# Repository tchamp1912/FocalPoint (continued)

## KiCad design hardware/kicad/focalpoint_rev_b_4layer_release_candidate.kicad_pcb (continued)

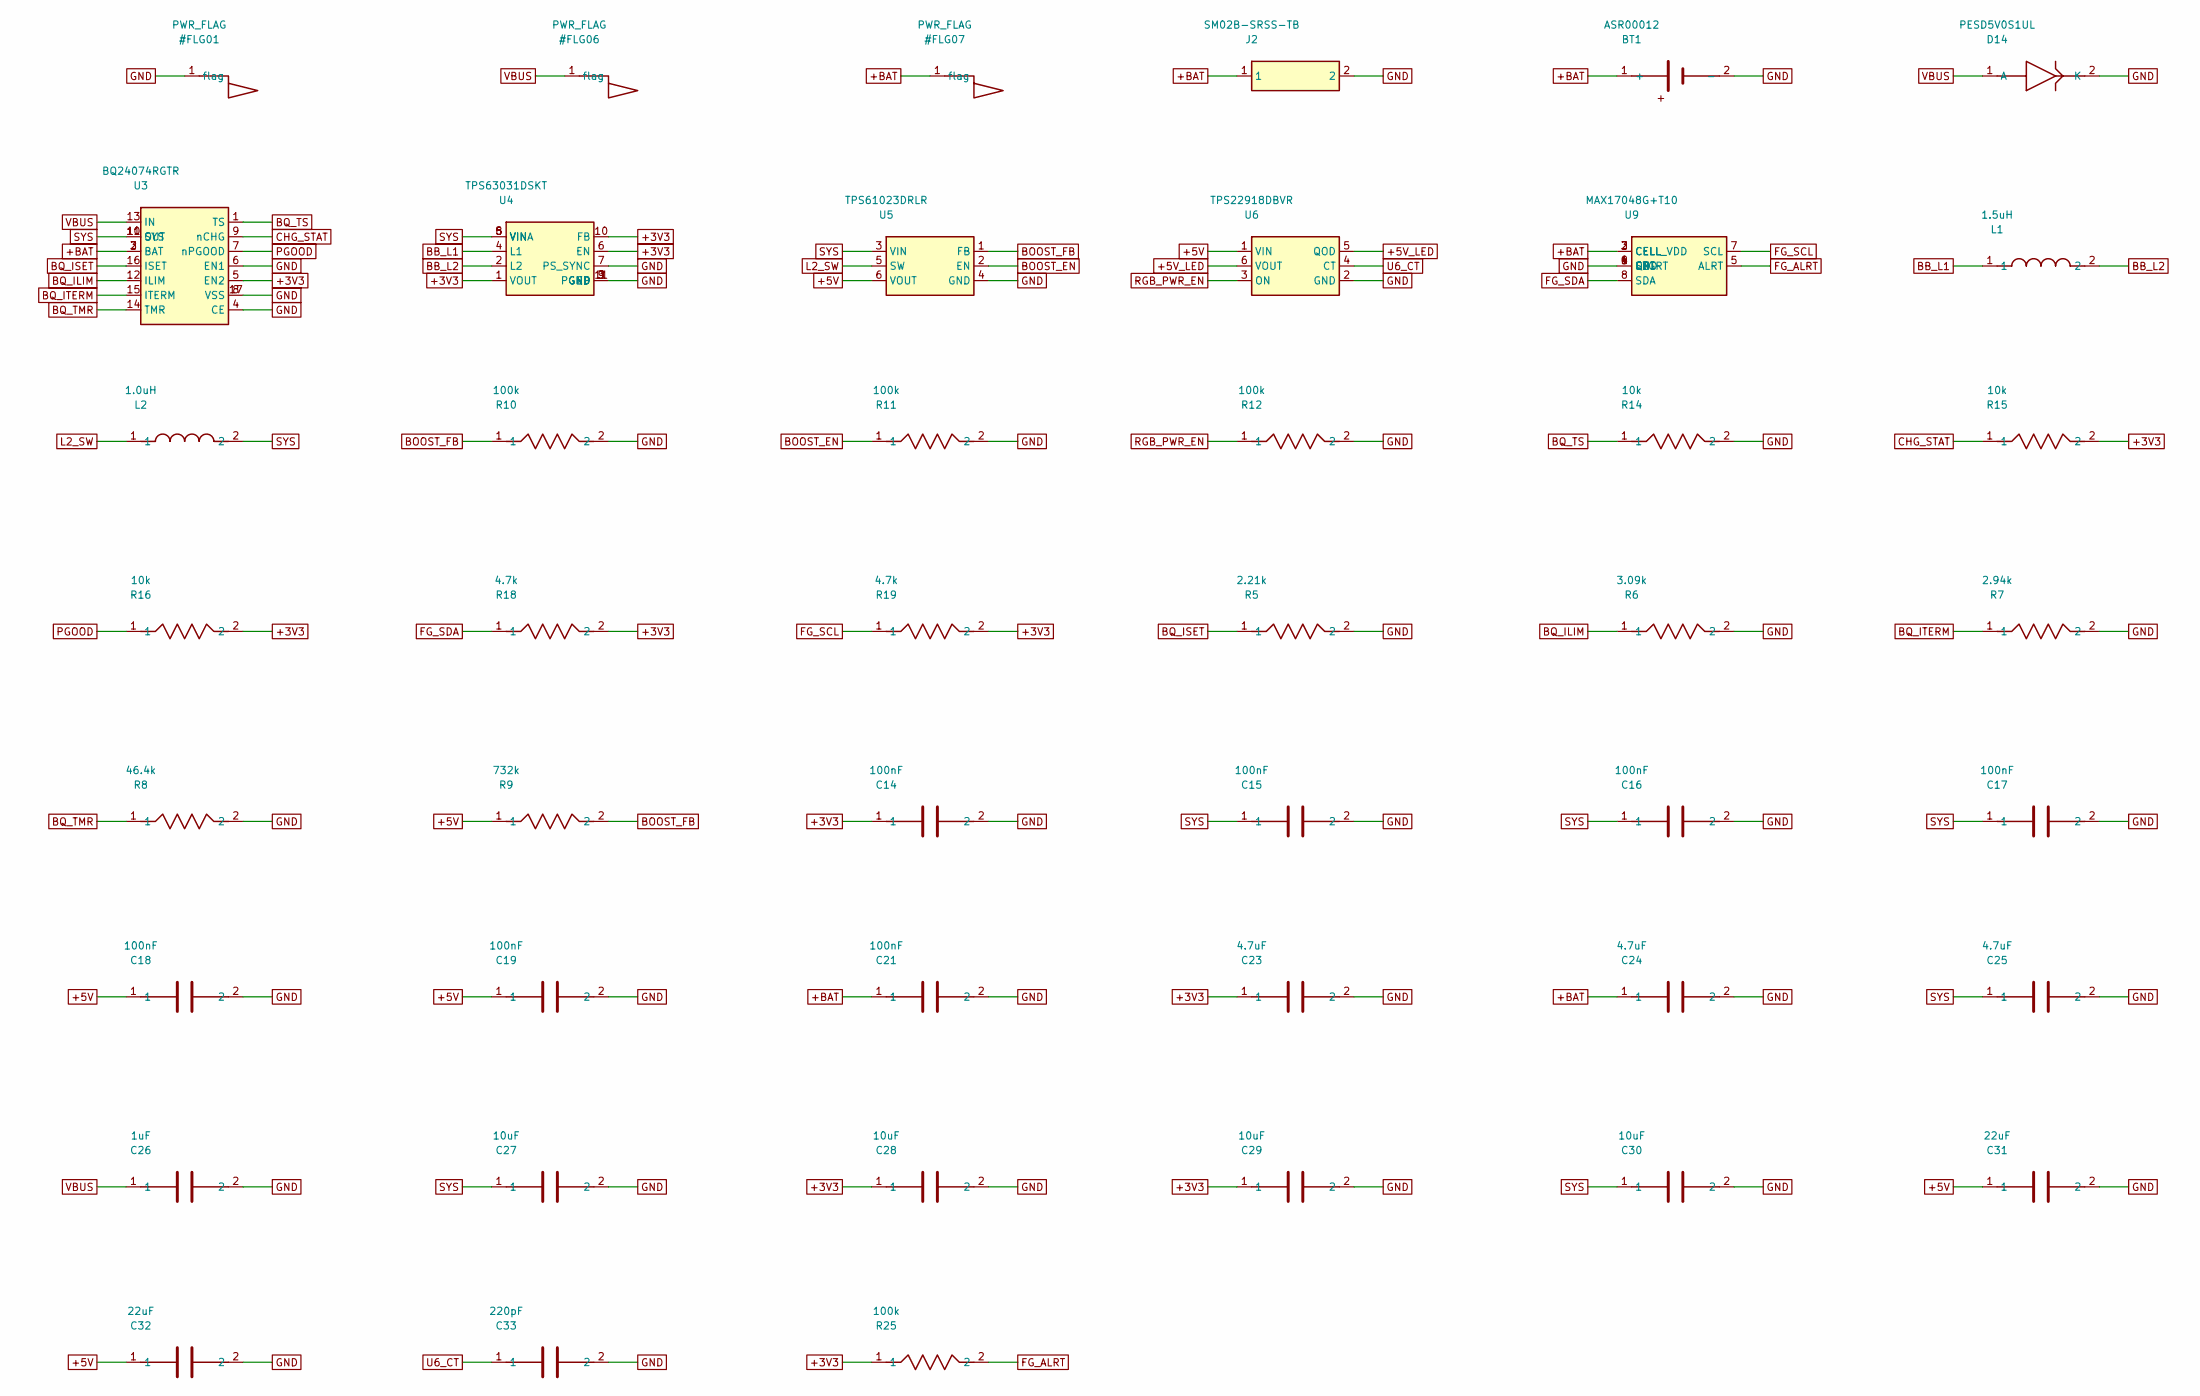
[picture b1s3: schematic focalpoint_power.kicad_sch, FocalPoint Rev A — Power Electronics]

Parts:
BT1: ASR00012
C14, C15, C16, C17, C18, C19, C21: 100nF; C_0603_1608Metric
C23, C24, C25: 4.7uF; C_0603_1608Metric
C26: 1uF; C_0603_1608Metric
C27, C28, C29, C30: 10uF; C_0603_1608Metric
C31, C32: 22uF; C_0603_1608Metric
C33: 220pF; C_0603_1608Metric
D14: PESD5V0S1UL; D_SOD-882
J2: SM02B-SRSS-TB; JST_SH_SM02B-SRSS-TB_1x02-1MP_P1.00mm_Horizontal
L1: 1.5uH; L_Sunlord_SWPA3015S
L2: 1.0uH; L_Sunlord_MWSA0402S
R5: 2.21k; R_0603_1608Metric
R6: 3.09k; R_0603_1608Metric
R7: 2.94k; R_0603_1608Metric
R8: 46.4k; R_0603_1608Metric
R9: 732k; R_0603_1608Metric
R10, R11, R12, R25: 100k; R_0603_1608Metric
R14, R15, R16: 10k; R_0603_1608Metric
R18, R19: 4.7k; R_0603_1608Metric
U3: BQ24074RGTR; VQFN-16-1EP_3x3mm_P0.5mm_EP1.68x1.68mm_ThermalVias
U4: TPS63031DSKT; WSON-10-1EP_2.5x2.5mm_P0.5mm_EP1.2x2mm_ThermalVias
U5: TPS61023DRLR; SOT-563
U6: TPS22918DBVR; SOT-23-6
U9: MAX17048G+T10; TDFN-8-1EP_2x2mm_P0.5mm_EP0.8x1.2mm

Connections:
+3V3: C14.1, C23.1, C28.1, C29.1, R15.2, R16.2, R18.2, R19.2, R25.1, U3.5 (EN2), U4.1 (VOUT), U4.6 (EN), U4.10 (FB); also elsewhere on the board
+5V: C18.1, C19.1, C31.1, C32.1, R9.1, U5.6 (VOUT), U6.1 (VIN); also elsewhere on the board
+5V_LED: U6.5 (QOD), U6.6 (VOUT); also elsewhere on the board
+BAT: BT1.1 (+), C21.1, C24.1, J2.1, U3.2 (BAT), U3.3 (BAT), U9.2 (CELL), U9.3 (CELL_VDD)
BB_L1: L1.1, U4.4 (L1)
BB_L2: L1.2, U4.2 (L2)
BOOST_EN: R11.1, U5.2 (EN); also elsewhere on the board
BOOST_FB: R9.2, R10.1, U5.1 (FB)
BQ_ILIM: R6.1, U3.12 (ILIM)
BQ_ISET: R5.1, U3.16 (ISET)
BQ_ITERM: R7.1, U3.15 (ITERM)
BQ_TMR: R8.1, U3.14 (TMR)
BQ_TS: R14.1, U3.1 (TS)
CHG_STAT: R15.1, U3.9 (nCHG); also elsewhere on the board
FG_ALRT: R25.2, U9.5 (ALRT); also elsewhere on the board
FG_SCL: R19.1, U9.7 (SCL); also elsewhere on the board
FG_SDA: R18.1, U9.8 (SDA); also elsewhere on the board
GND: BT1.2 (-), C14.2, C15.2, C16.2, C17.2, C18.2, C19.2, C21.2, C23.2, C24.2, C25.2, C26.2, C27.2, C28.2, C29.2, C30.2, C31.2, C32.2, C33.2, D14.2 (K), J2.2, R5.2, R6.2, R7.2, R8.2, R10.2, R11.2, R12.2, R14.2, U3.4 (CE), U3.6 (EN1), U3.8 (VSS), U3.17 (VSS), U4.3 (PGND), U4.7 (PS_SYNC), U4.9 (GND), U4.11 (EP), U5.4 (GND), U6.2 (GND), U9.1 (CTG), U9.4 (GND), U9.6 (QSTRT), U9.9 (EP); also elsewhere on the board
L2_SW: L2.1, U5.5 (SW)
PGOOD: R16.1, U3.7 (nPGOOD); also elsewhere on the board
RGB_PWR_EN: R12.1, U6.3 (ON); also elsewhere on the board
SYS: C15.1, C16.1, C17.1, C25.1, C27.1, C30.1, L2.2, U3.10 (SYS), U3.11 (OUT), U4.5 (VIN), U4.8 (VINA), U5.3 (VIN)
U6_CT: C33.1, U6.4 (CT)
VBUS: C26.1, D14.1 (A), U3.13 (IN); also elsewhere on the board

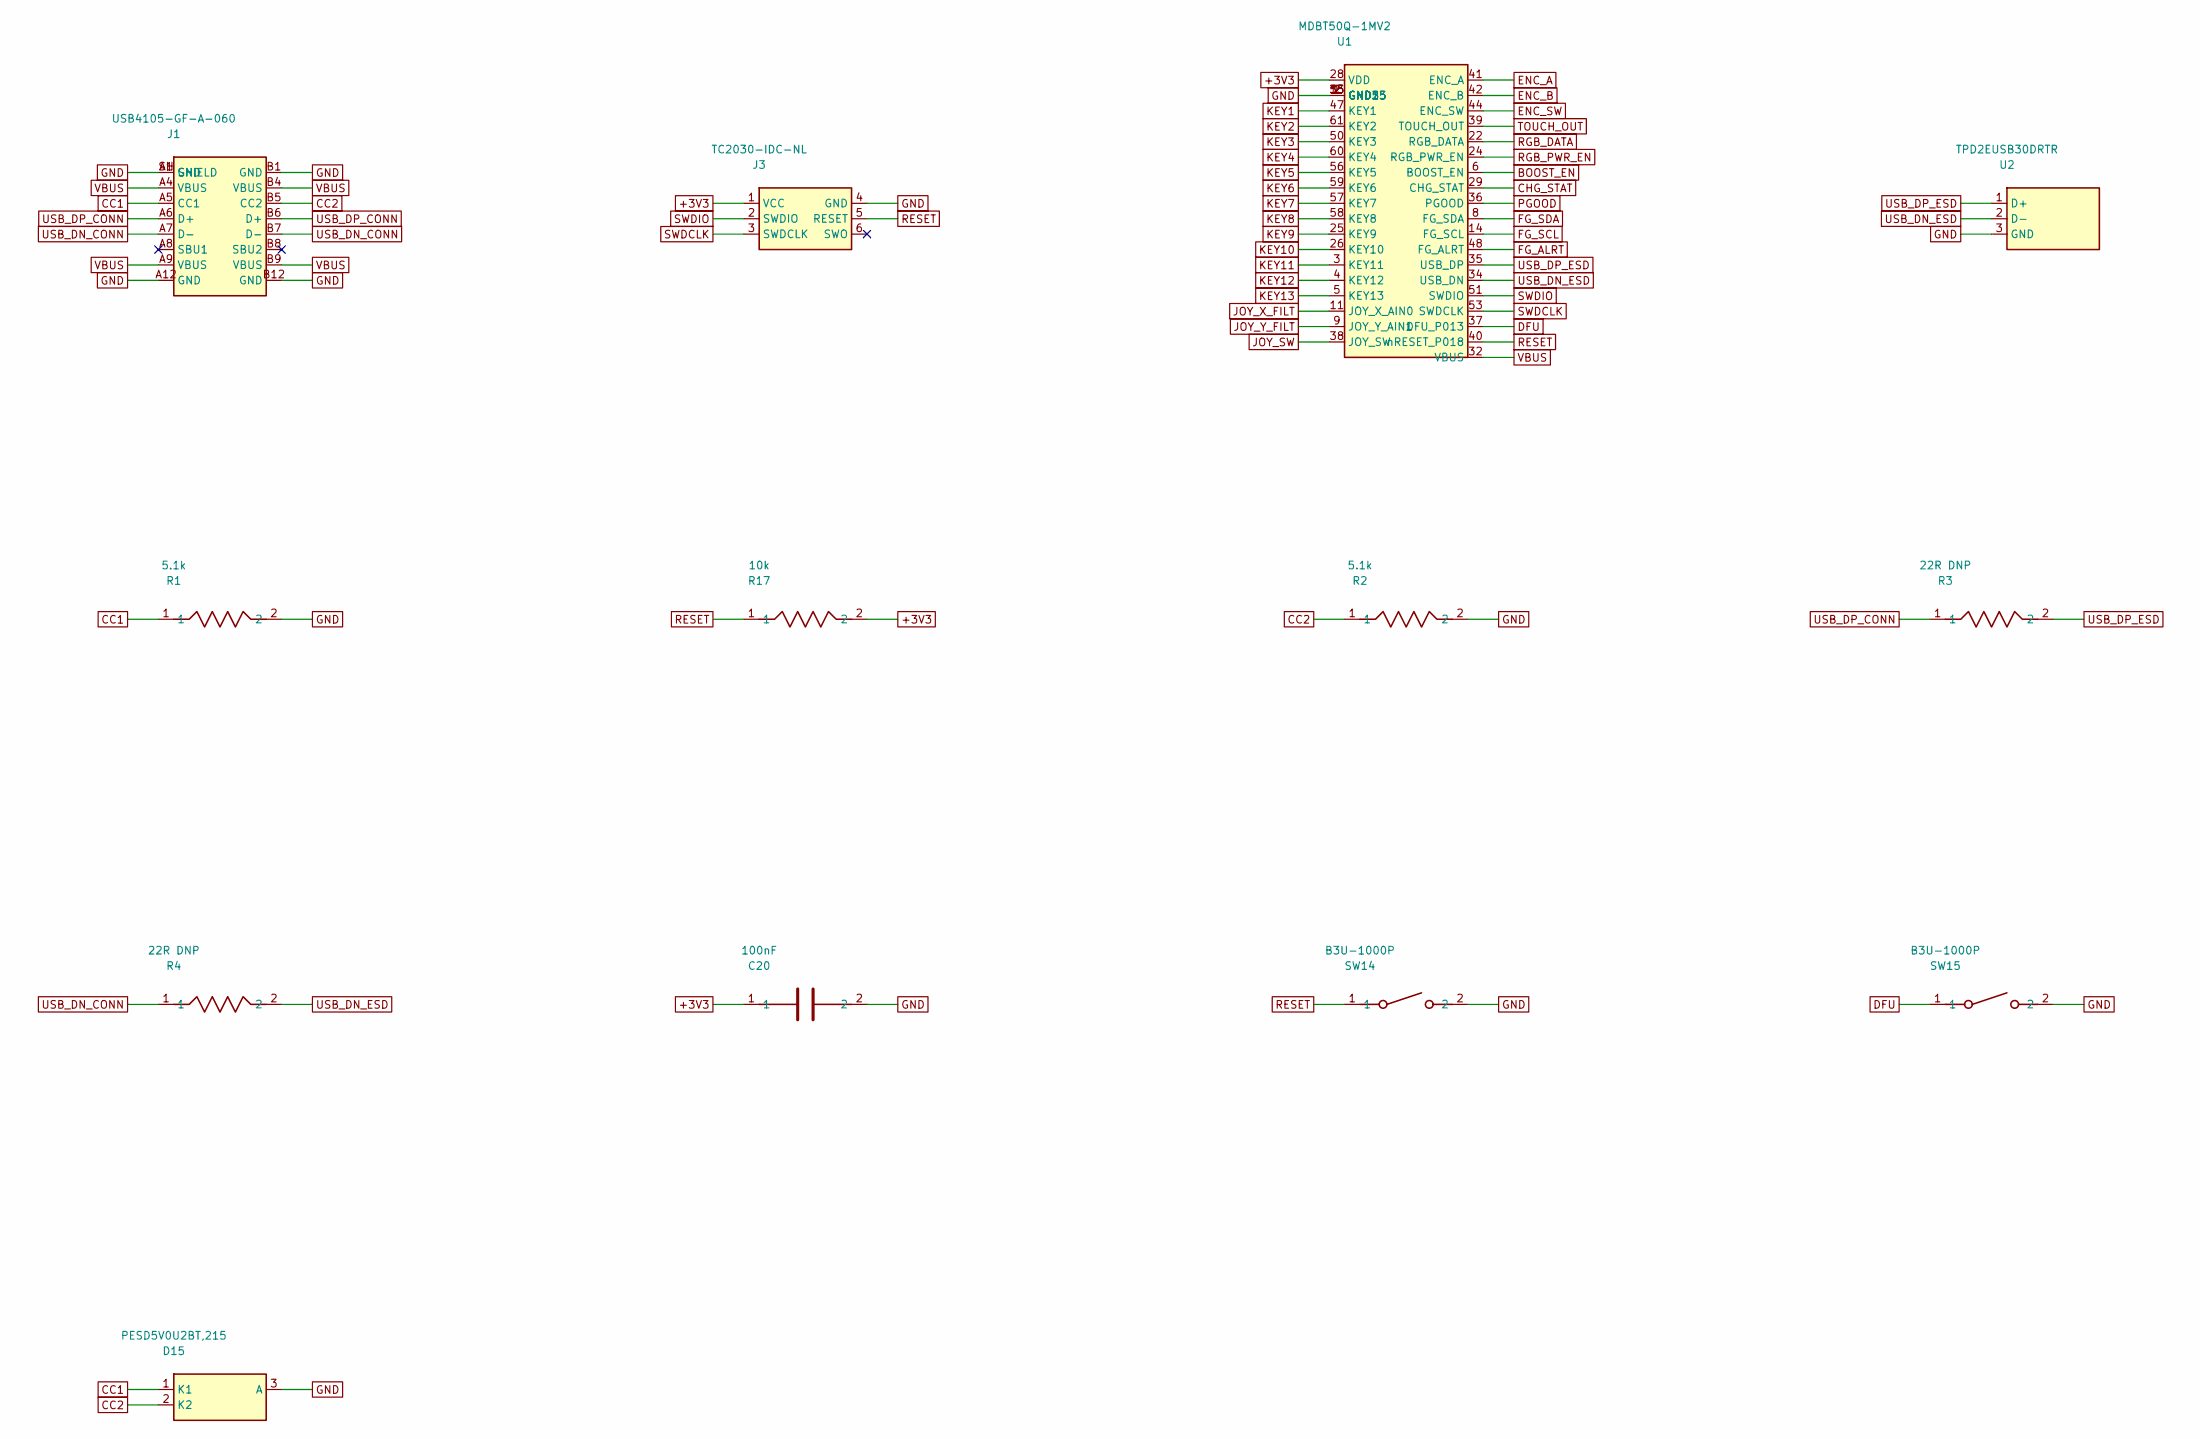
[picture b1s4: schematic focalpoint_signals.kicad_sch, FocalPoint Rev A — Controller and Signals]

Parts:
C20: 100nF; C_0603_1608Metric
D15: PESD5V0U2BT,215; SOT-23
J1: USB4105-GF-A-060; USB_C_Receptacle_GCT_USB4105-xx-A_16P_TopMnt_Horizontal
J3: TC2030-IDC-NL; Tag-Connect_TC2030-IDC-NL_2x03_P1.27mm_Vertical
R1, R2: 5.1k; R_0603_1608Metric
R3, R4: 22R DNP; R_0603_1608Metric
R17: 10k; R_0603_1608Metric
SW14, SW15: B3U-1000P; SW_SPST_B3U-1000P
U1: MDBT50Q-1MV2; Raytac_MDBT50Q
U2: TPD2EUSB30DRTR; Texas_DRT-3

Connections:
+3V3: C20.1, J3.1 (VCC), R17.2, U1.28 (VDD); also elsewhere on the board
BOOST_EN: U1.6 (BOOST_EN); also elsewhere on the board
CC1: D15.1 (K1), J1.A5 (CC1), R1.1
CC2: D15.2 (K2), J1.B5 (CC2), R2.1
CHG_STAT: U1.29 (CHG_STAT); also elsewhere on the board
DFU: SW15.1, U1.37 (DFU_P013)
ENC_A: U1.41 (ENC_A); also elsewhere on the board
ENC_B: U1.42 (ENC_B); also elsewhere on the board
ENC_SW: U1.44 (ENC_SW); also elsewhere on the board
FG_ALRT: U1.48 (FG_ALRT); also elsewhere on the board
FG_SCL: U1.14 (FG_SCL); also elsewhere on the board
FG_SDA: U1.8 (FG_SDA); also elsewhere on the board
GND: C20.2, D15.3 (A), J1.A1 (GND), J1.A12 (GND), J1.B1 (GND), J1.B12 (GND), J1.SH (SHIELD), J3.4 (GND), R1.2, R2.2, SW14.2, SW15.2, U1.1 (GND), U1.2 (GND2), U1.15 (GND15), U1.33 (GND33), U1.55 (GND55), U2.3 (GND); also elsewhere on the board
JOY_SW: U1.38 (JOY_SW); also elsewhere on the board
JOY_X_FILT: U1.11 (JOY_X_AIN0); also elsewhere on the board
JOY_Y_FILT: U1.9 (JOY_Y_AIN1); also elsewhere on the board
KEY1: U1.47 (KEY1); also elsewhere on the board
KEY2: U1.61 (KEY2); also elsewhere on the board
KEY3: U1.50 (KEY3); also elsewhere on the board
KEY4: U1.60 (KEY4); also elsewhere on the board
KEY5: U1.56 (KEY5); also elsewhere on the board
KEY6: U1.59 (KEY6); also elsewhere on the board
KEY7: U1.57 (KEY7); also elsewhere on the board
KEY8: U1.58 (KEY8); also elsewhere on the board
KEY9: U1.25 (KEY9); also elsewhere on the board
KEY10: U1.26 (KEY10); also elsewhere on the board
KEY11: U1.3 (KEY11); also elsewhere on the board
KEY12: U1.4 (KEY12); also elsewhere on the board
KEY13: U1.5 (KEY13); also elsewhere on the board
PGOOD: U1.36 (PGOOD); also elsewhere on the board
RESET: J3.5 (RESET), R17.1, SW14.1, U1.40 (nRESET_P018)
RGB_DATA: U1.22 (RGB_DATA); also elsewhere on the board
RGB_PWR_EN: U1.24 (RGB_PWR_EN); also elsewhere on the board
SWDCLK: J3.3 (SWDCLK), U1.53 (SWDCLK)
SWDIO: J3.2 (SWDIO), U1.51 (SWDIO)
TOUCH_OUT: U1.39 (TOUCH_OUT); also elsewhere on the board
USB_DN_CONN: J1.A7 (D-), J1.B7 (D-), R4.1
USB_DN_ESD: R4.2, U1.34 (USB_DN), U2.2 (D-)
USB_DP_CONN: J1.A6 (D+), J1.B6 (D+), R3.1
USB_DP_ESD: R3.2, U1.35 (USB_DP), U2.1 (D+)
VBUS: J1.A4 (VBUS), J1.A9 (VBUS), J1.B4 (VBUS), J1.B9 (VBUS), U1.32 (VBUS); also elsewhere on the board

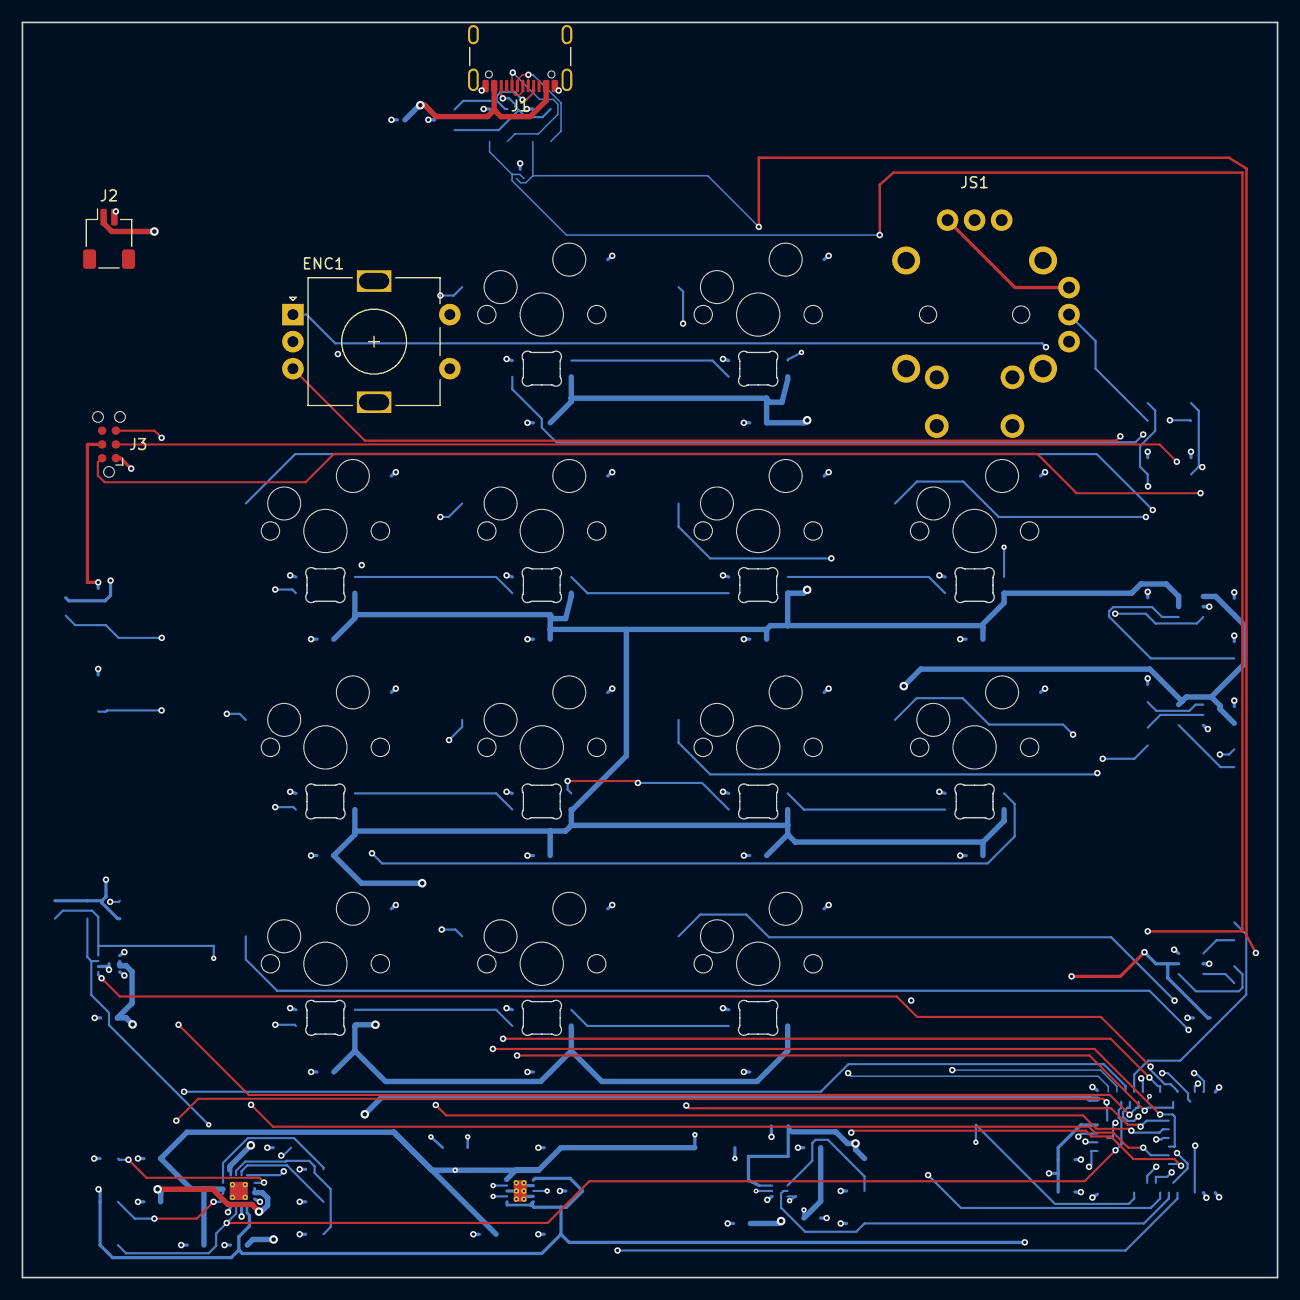
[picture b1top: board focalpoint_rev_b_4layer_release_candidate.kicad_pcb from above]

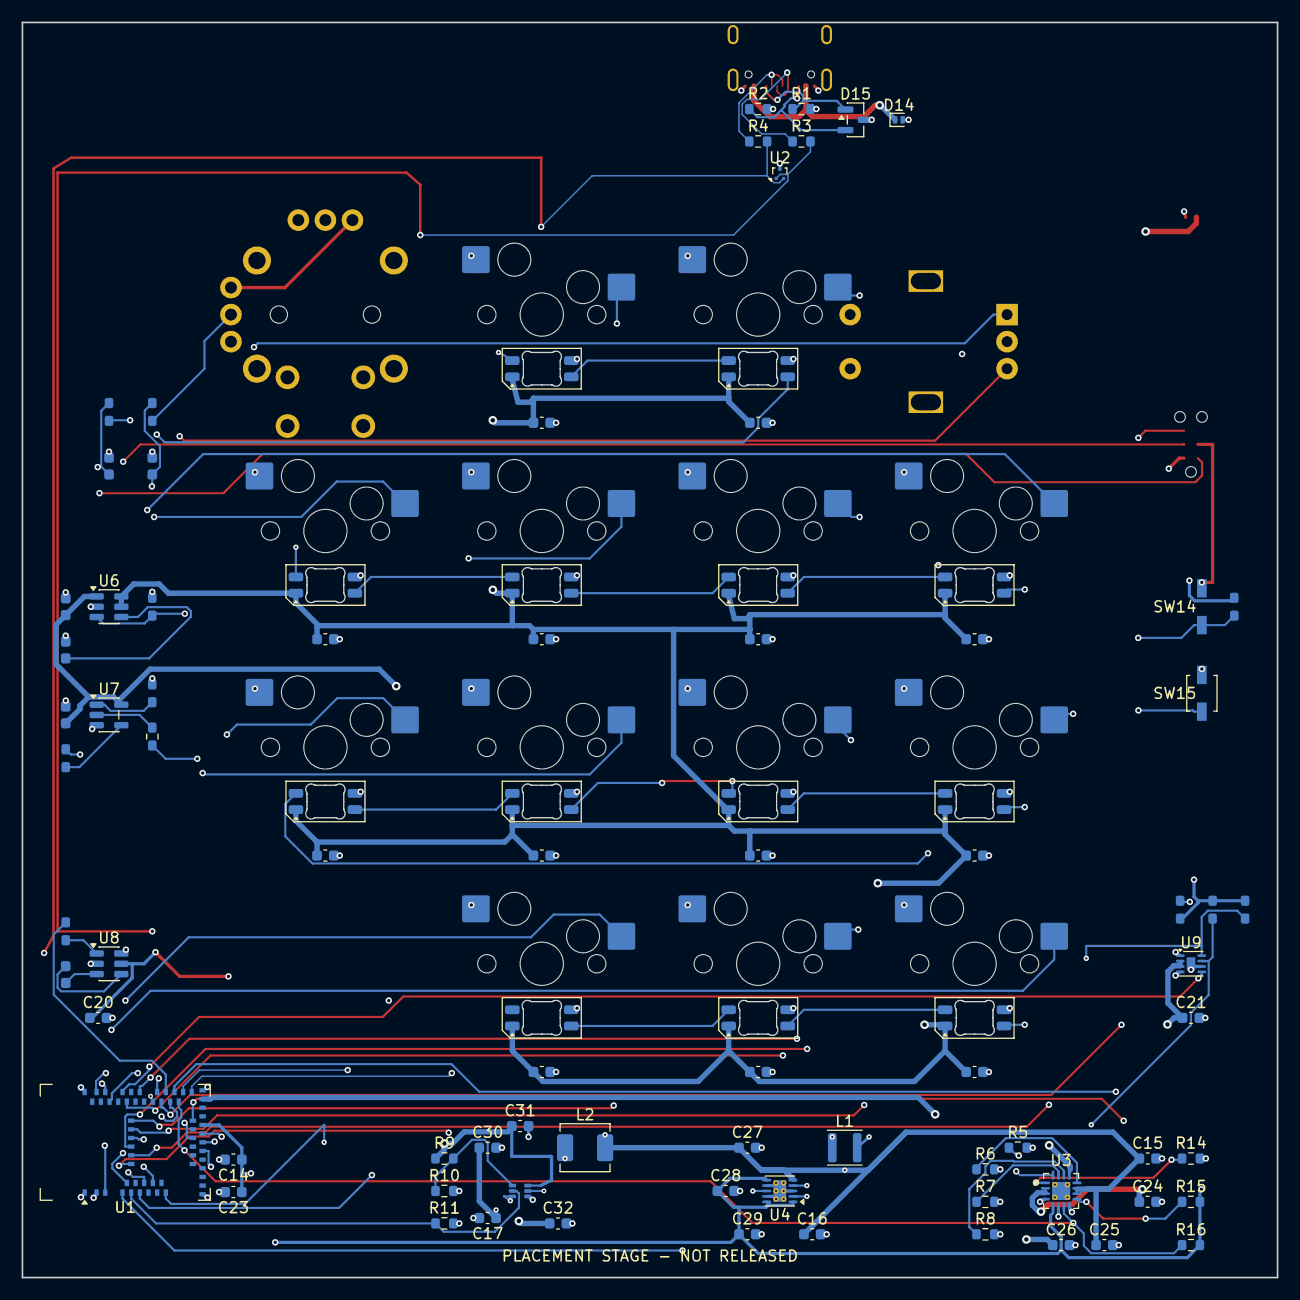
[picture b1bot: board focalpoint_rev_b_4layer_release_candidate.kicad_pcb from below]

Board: 4 copper layers, 116.0 x 116.0 mm, 106 parts (101 on the bottom side), 76 nets.

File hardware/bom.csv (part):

Category,Function,Manufacturer,MPN,Qty_per_unit,Two_device_buy_qty,Assembly,LCSC,Validation,Notes,Designators
IC,MCU radio,Raytac,MDBT50Q-1MV2,1,2,JLC SMT,C5118826,V1-V2,Custom footprint and antenna keepout; live JLC match pending,U1
Connector,USB-C,GCT,USB4105-GF-A-060,1,2,JLC hybrid,C3025063,V1-V2,Case integration pending,J1
Protection,USB data ESD,Texas Instruments,TPD2EUSB30DRTR,1,2,JLC SMT,C97502,V1-V2,Never substitute C3011197,U2
Protection,VBUS TVS,Nexperia,PESD5V0S1UL,1,2,JLC SMT,C85402,V1-V2,LCSC lists packing suffix 315; live stock pending,D14
Protection,USB CC ESD,Nexperia,"PESD5V0U2BT,215",1,2,JLC SMT,C85399,V1-V2,dual 5V bidirectional ESD on CC1/CC2; SOT-23 pin 1/2 protected and pin 3 common to GND matches PCB; exact LCSC listing and Nexperia pinout verified 2026-07-30,D15
Power,Charger power path,Texas Instruments,BQ24074RGTR,1,2,JLC SMT,C54313,V1-V2,400mA charge thermal test pending; programming network verified vs TI SLUS810N 2026-07-28,U3
Power,3V3 buck-boost,Texas Instruments,TPS63031DSKT,1,2,JLC SMT,C15516,V1-V2,Exact layout required; LCSC stocks reel suffix DSKR (same device),U4
Power,5V RGB boost,Texas Instruments,TPS61023DRLR,1,2,JLC SMT,C919459,V1-V2,Exact layout required,U5
Power,RGB load switch,Texas Instruments,TPS22918DBVR,1,2,JLC SMT,C131941,V1-V2,Default off; retention rationale in kicad/DECISIONS.md,U6
Logic,RGB level buffer,Texas Instruments,SN74AHCT1G125DBVR,1,2,JLC SMT,C7484,V1-V2,No AHC substitution; supply from always-on 5V upstream of TPS22918,U7
LED,RGB LED,OPSCO,SK6812MINI-E 12mA,13,26,JLC bottom SMT,C5149201,V1-V2,JLC may add unavoidable attrition; reverse mount MSL5a; confirm 12mA/channel from C5149201 datasheet — not an orderable MPN suffix,LED1-LED13
Sensor,Touch,Microchip,AT42QT1010-TSHR,1,2,JLC SMT,C74512,V1-V2,Physical test pending,U8
Sensor,Fuel gauge,Analog Devices,MAX17048G+T10,1,2,JLC SMT,C2682616,V1-V2,Validate with cell,U9
Battery,Protected LiPo,TinyCircuits,ASR00012,1,2,User,,V1-V2,1000mAh 42x39x5.5mm JST-SH; verify pigtail polarity (unstandardized); silkscreen polarity marks required,BT1 (off-board)
Connector,Battery header,JST,SM02B-SRSS-TB(LF)(SN),1,2,JLC SMT,C160402,V1-V2,Verify polarity; SH contacts rated ~1A — zero margin at pack limit,J2
Control,Joystick,Alps Alpine,RKJXV122400R,1,2,User THT,C918854,V1,Rev A baseline; local footprint from Alps Drawing No.1 update 2510; hand-solder all terminals and four lugs; verify physical sample before release,JS1
Control,Encoder,Alps Alpine,EC11E15244G1,1,2,User THT,C370970,V1-V2,CAD check pending,ENC1
Control,Encoder knob,Mentor,505.6131,1,2,User,,V1-V2,12mm diameter,KNOB1
Control,Hot-swap socket,Kailh,CPG151101S11,13,26,JLC bottom SMT,C2803348,V1-V3 footprint,Local footprint from KHA-PG1511-094EN Rev B / KH-PS-1607-10 Rev B; JLC placement acceptance pending,HS1-HS13
Control,Tactile MX switch,Kailh,CPG151101D280,13,26,User,,V1,Exactly two devices,SW1-SW13 (removable)
Keycap,Clear DSA 1u,Adafruit,5068,12,2 packs,User,,V1-V2,Twelve per pack; exact two-device quantity,KC1-KC12
Keycap,Ceramic 1u,Cerakey,F SET-RX1U,1,1 pack,User,,V1,Four pack,KC13
Switch,Reset boot,Omron,B3U-1000P,2,4,JLC SMT,C231329,V1,Case access pending,SW14-SW15
Programming,SWD,Tag-Connect,TC2030-IDC-NL,1,1 footprint,None,,V1,External cable required,J3 (footprint only)
Inductor,3V3 inductor,Sunlord,SWPA3015S1R5MT,1,2,JLC SMT,C83434,V1-V2 prov,1.5uH 3.0x3.0x1.5mm Isat>=2.3A DCR 65mR max; provisional equivalent of Coilcraft LPS3015-152MLB — verify L/Isat/DCR vs TPS63031 datasheet,L1
Inductor,RGB inductor,Sunlord,MWSA0402S-1R0MT,1,2,JLC SMT,C408332,V1-V2 prov,1uH 4.4x4.2mm Isat 7A rated 6A DCR 27mR; provisional equivalent of Coilcraft XEL4030-102ME — verify L/Isat/DCR vs TPS61023 datasheet,L2
Resistor,USB CC,Yageo,RC0603FR-075K1L,2,4,JLC SMT,C105580,V1-V2,5.1k 1%; exact LCSC MPN/package match verified 2026-07-30,R1-R2
Resistor,USB data series DNP,Yageo,RC0603FR-0722RL,2,4,DNP,,V1-V2 prov,22R 1%; do not populate for Rev A; 0R copper bypasses carry D+/D- and these footprints are tuning options,R3-R4
Resistor,BQ ISET,Yageo,RC0603FR-072K21L,1,2,JLC SMT,C273748,V1-V2,2.21k 1%; 403mA fast charge (KISET 890 AΩ); exact LCSC match verified 2026-07-30,R5
Resistor,BQ ILIM,Yageo,RC0603FR-073K09L,1,2,JLC SMT,C185334,V1-V2,3.09k 1%; ~521mA typ input limit (KILIM 1610 AΩ; EN2=1/EN1=0); exact LCSC match verified 2026-07-30,R6
Resistor,BQ ITERM,TA-I Tech,RMS06FT2941,1,2,JLC SMT,C209098,V1-V2,2.94k 1% 0603 stocked equivalent; ITERM pin 15 verified on BQ24074 (SLUS810N); ~40mA = 10% of fast charge,R7
Resistor,BQ timer,Yageo,RC0603FR-0746K4L,1,2,JLC SMT,C165747,V1-V2,46.4k 1%; ~37min precharge / ~6.2h fast-charge timeout; exact LCSC match verified 2026-07-30,R8
Resistor,Boost FB top,Yageo,RC0603FR-07732KL,1,2,JLC SMT,C246003,V1-V2,732k 1%; exact LCSC match verified 2026-07-30,R9
Resistor,100k network,Yageo,RC0603FR-07100KL,4,8,JLC SMT,C14675,V1-V2,Boost FB bottom and RGB EN/QOD/OE pulls; exact LCSC match verified 2026-07-30,R10-R13
Resistor,10k network,Yageo,RC0603FR-0710KL,4,8,JLC SMT,C98220,V1-V2,Charger TS and reset/boot/control pulls; exact LCSC match verified 2026-07-30,R14-R17
Resistor,I2C pullups,Yageo,RC0603FR-074K7L,2,4,JLC SMT,C99782,V1-V2,4.7k 1% for fuel gauge; exact LCSC match verified 2026-07-30,R18-R19
Resistor,RGB input and touch series,Yageo,RC0603FR-071KL,2,4,JLC SMT,C22548,V1-V2,1k 1%; corrected to Yageo's orderable MPN and exact LCSC match verified 2026-07-30,R20-R21
Resistor,RGB data,Yageo,RC0603FR-0733RL,1,2,JLC SMT,C108661,V1-V2,33R 1%; exact LCSC match verified 2026-07-30,R22
Resistor,Joystick SAADC series,Yageo,RC0603FR-071KL,2,4,JLC SMT,C22548,V1-V2,1k 1% series to SAADC per axis (JOY_X/JOY_Y); corrected orderable MPN; pairs with C35-C36 fc~16kHz,R23-R24
Resistor,FG_ALRT pullup,Yageo,RC0603FR-07100KL,1,2,JLC SMT,C14675,V1-V2,100k 1% pull-up for MAX17048 ALRT open-drain (not shared with SDA/SCL); exact LCSC match verified 2026-07-30,R25
Capacitor,100nF bypass,Murata,GRM188R71C104KA01D,21,42,JLC SMT,C45000,V1-V2 prov,Final captured set: C1-C21; cross-checked against the release PCB,C1-C21
Capacitor,Radio bulk 4.7uF,Murata,GRM188R60J475KE19D,1,2,JLC SMT,C71631,V1-V2 prov,At Raytac supply input,C23
Capacitor,BQ 4.7uF,Murata,GRM188R60J475KE19D,2,4,JLC SMT,C71631,V1-V2 prov,6.3V X5R,C24-C25
Capacitor,BQ 1uF,Murata,GRM188R61A105KA61D,1,2,JLC SMT,C86012,V1-V2,10V X5R; exact LCSC MPN/package match verified 2026-07-30,C26
Capacitor,3V3 10uF,Murata,GRM188B31A106ME69D,3,6,JLC SMT,C162265,V1-V2,10V 0603; package-compatible replacement for the earlier NRND part; exact LCSC match verified 2026-07-30,C27-C29
Capacitor,Boost input 10uF,Murata,GRM188B31A106ME69D,1,2,JLC SMT,C162265,V1-V2,10V 0603 X5R; replaces the footprint-incompatible 0805 choice; exact LCSC match verified 2026-07-30,C30
Capacitor,Boost output 22uF,Samsung Electro-Mechanics,CL10A226MP7LUNC,2,4,JLC SMT,C2762595,V1-V2,10V X5R 0603; replaces the obsolete footprint-incompatible 1206 choice; two parallel capacitors retained; verify effective capacitance during 5V rail load test,C31-C32
Capacitor,Load switch CT,Murata,GRM1885C1H221GA01D,1,2,JLC SMT,C440180,V1-V2,220pF C0G 0603 ±2%; replaces the footprint-incompatible 0402 choice; exact LCSC match verified 2026-07-30,C33
Capacitor,Touch Cs,Murata,GRM188R71H103KA01D,1,2,JLC SMT,C77053,V1-V2,10nF X7R; exact LCSC match verified 2026-07-30,C34
Capacitor,Joystick SAADC shunt,Murata,GRM188R71H103KA01D,2,4,JLC SMT,C77053,V1-V2,10nF X7R shunt to GND per axis; exact LCSC match verified 2026-07-30,C35-C36
Mechanical,Insert,McMaster-Carr,94180A321,4,8,User,,V1,Supplier pack minimum may create excess; boss redesign required,INS1-INS4
Mechanical,Screw,TR Fastenings,TR00004792-000,4,8,User,,V1,M2.5x8 ISO 7380-1 A2 stainless; fit validation required,SCR1-SCR4
Mechanical,Silicone sheet,McMaster-Carr,8525T575,1 disc,1 sheet,User,,V1-V2,Cut two 72mm discs; 60A 1/16in sheet,FOOT1
Mechanical,Transfer adhesive,3M,467MP,1 disc,1 sheet or roll,User,,V1-V2,Cut two 72mm adhesive discs,ADH1
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
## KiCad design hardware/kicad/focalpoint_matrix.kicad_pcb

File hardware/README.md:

# FocalPoint hardware

The first assembled FocalPoint is a square wireless MX macropad, not a wired RP2040
derivative. The Keychron V1 Max firmware remains the Phase 0 test platform for
the host loop while this hardware is developed.

## Rev A definition of done

- A visual 4×4 input lattice with the encoder top-left, analog joystick
  top-right, capacitive touch bottom-right, and 13 RGB MX keys filling every
  other cell. Twelve caps are clear/frosted PC and one is ceramic. All controls are
  dynamically assignable in firmware/host configuration. Use south-facing LED
  geometry: Cerakey-style Cherry-profile caps can collide with north-facing
  switch LEDs, and ceramic itself will not transmit the status light.
- nRF52840-module-based board that pairs as BLE HID and accepts daemon status
  updates through a versioned FocalPoint BLE GATT transport.
- USB-C supports charging, USB HID/Raw HID, recovery, and firmware updates.
- Protected LiPo, charger with power-path management, battery connector, and
  firmware RGB current limit.
- Printed two-piece case with a protected battery pocket, a radio antenna
  keep-out/RF window, no-support FDM orientation, and accessible reset/boot
  control.
- One real agent session works end-to-end while unplugged: daemon state updates
  reach LEDs and input events reach the daemon.

## Work order

1. Generate and physically validate the Ergogen plate in `ergogen/`.
2. Buy a small cap/switch sample set before finalizing plate height and case
   clearance.
3. Choose the certified nRF52840 module and place its official antenna
   keep-out on the KiCad board before placing the battery or screws.
4. Design the charger/power path and verify thermal/current margins before
   routing the RGB rail.
5. Add the logical BLE transport to `PROTOCOL.md`, then implement firmware and
   daemon transport selection together.
6. Print and test the enclosure before ordering five Rev A boards.

The PCB project, manufacturing files, and BOM belong here once schematic
capture starts. Do not treat generated Ergogen output as a production-ready
electrical design.

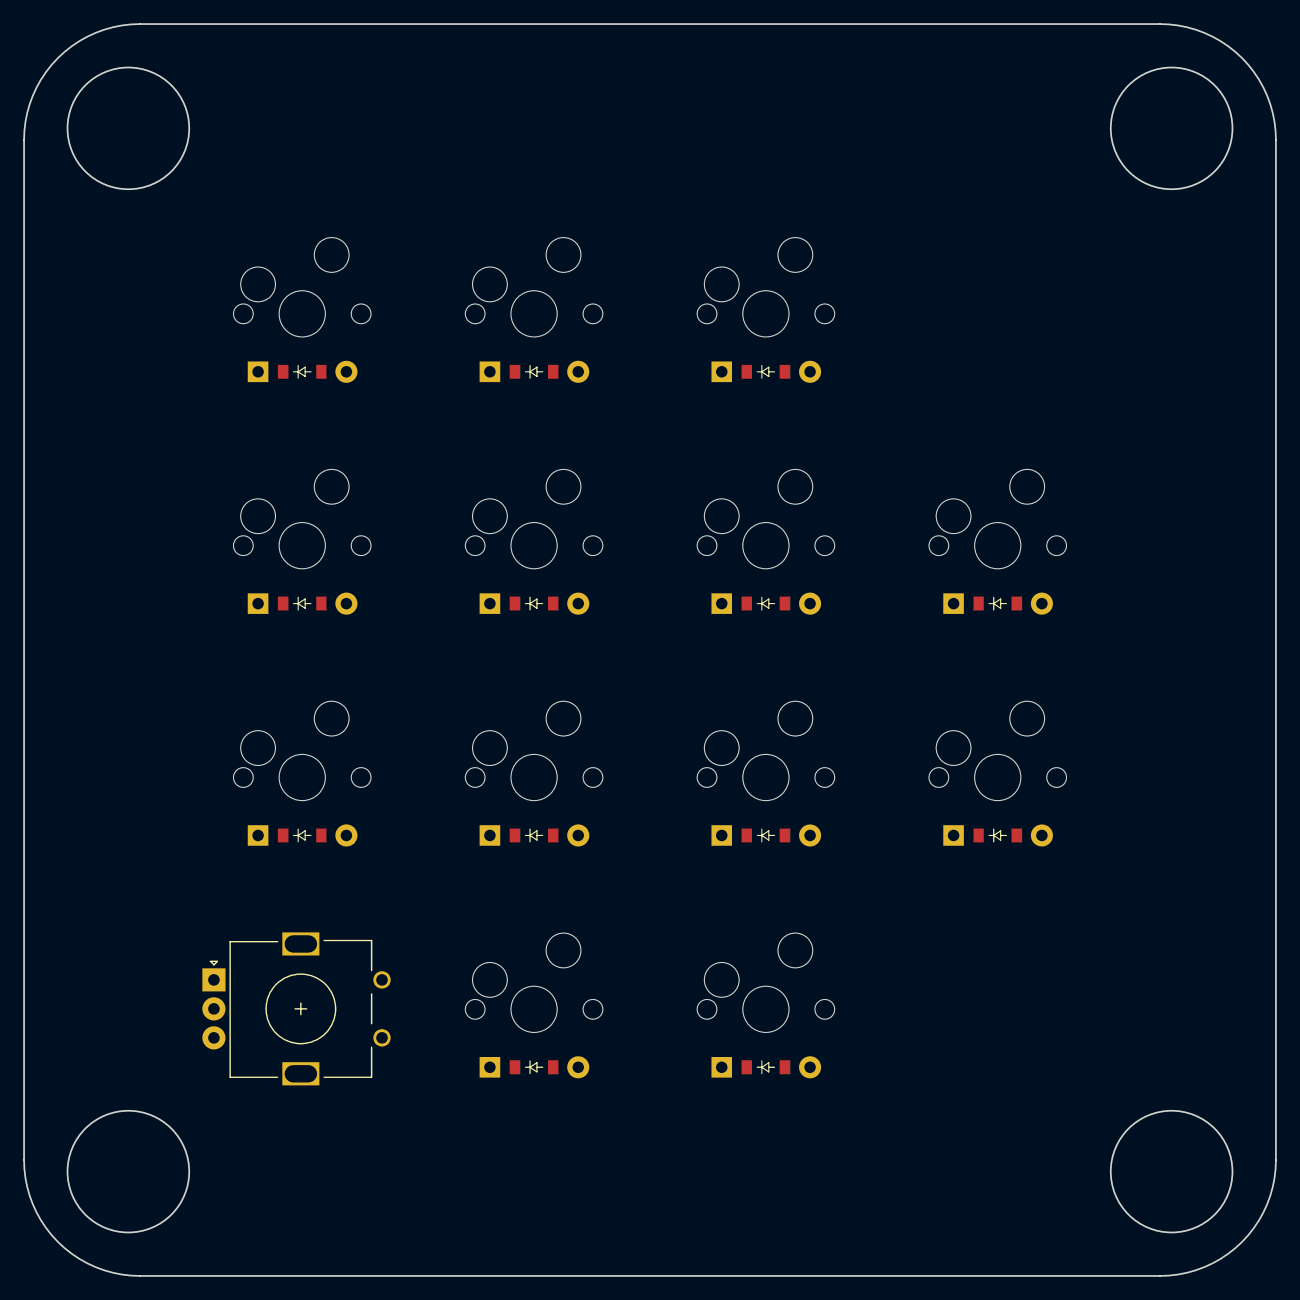
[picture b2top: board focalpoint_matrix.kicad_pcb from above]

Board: 2 copper layers, 108.0 x 108.0 mm, 27 parts (0 on the bottom side), 22 nets, no tracks yet.

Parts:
D1, D2, D3, D4, D5, D6, D7, D8, D9, D10, D11, D12, D13: ComboDiode
ROT1: rotary_encoder
S1, S2, S3, S4, S5, S6, S7, S8, S9, S10, S11, S12, S13: MX

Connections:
C0: S1.2, S2.2, S11.2
C1: S3.2, S4.2, S9.2, S12.2
C2: S5.2, S6.2, S10.2, S13.2
C3: S7.2, S8.2
GND: ROT1.2, ROT1.B
R0: D9.1, D10.1
R1: D1.1, D3.1, D5.1, D7.1
R2: D2.1, D4.1, D6.1, D8.1
R3: D11.1, D12.1, D13.1
ceramic_row_1: D10.2, S10.1
clear_row_1: D9.2, S9.1
col_1_row_2: D1.2, S1.1
col_1_row_3: D2.2, S2.1
col_1_row_4: D11.2, S11.1
col_2_row_2: D3.2, S3.1
col_2_row_3: D4.2, S4.1
col_2_row_4: D12.2, S12.1
col_3_row_2: D5.2, S5.1
col_3_row_3: D6.2, S6.1
col_3_row_4: D13.2, S13.1
col_4_row_2: D7.2, S7.1
col_4_row_3: D8.2, S8.1

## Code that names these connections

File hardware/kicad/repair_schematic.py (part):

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
    # Add the BOM-revision circuits in unused sheet space.
    additions = "".join([
        two_pin("R23", "1k", "R", 25.4, 558.8, "JOY_X", "JOY_X_FILT", "Resistor_SMD:R_0603_1608Metric"),
        two_pin("R24", "1k", "R", 76.2, 558.8, "JOY_Y", "JOY_Y_FILT", "Resistor_SMD:R_0603_1608Metric"),
        two_pin("C35", "10nF", "C", 127.0, 558.8, "JOY_X_FILT", "GND", "Capacitor_SMD:C_0603_1608Metric"),
        two_pin("C36", "10nF", "C", 177.8, 558.8, "JOY_Y_FILT", "GND", "Capacitor_SMD:C_0603_1608Metric"),
        two_pin("R25", "100k", "R", 228.6, 558.8, "+3V3", "FG_ALRT", "Resistor_SMD:R_0603_1608Metric"),
        dual_tvs_instance(279.4, 558.8),
    ])
    # Add the D15 cached library definition inside lib_symbols.
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    next_symbol = text.index("\n\t(symbol", l2_end)
    l2_connections = text[l2_end:next_symbol]
    l2_connections = l2_connections.replace(
        '(global_label "+5V"', '(global_label "SYS"', 1
    )
    text = text[:l2_end] + l2_connections + text[next_symbol:]

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

if __name__ == "__main__":
    if "--fix-package-pinouts" in sys.argv:
        fix_package_pinouts_after_review()
    elif "--fix-u1-power" in sys.argv:
        fix_u1_power_after_review()
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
